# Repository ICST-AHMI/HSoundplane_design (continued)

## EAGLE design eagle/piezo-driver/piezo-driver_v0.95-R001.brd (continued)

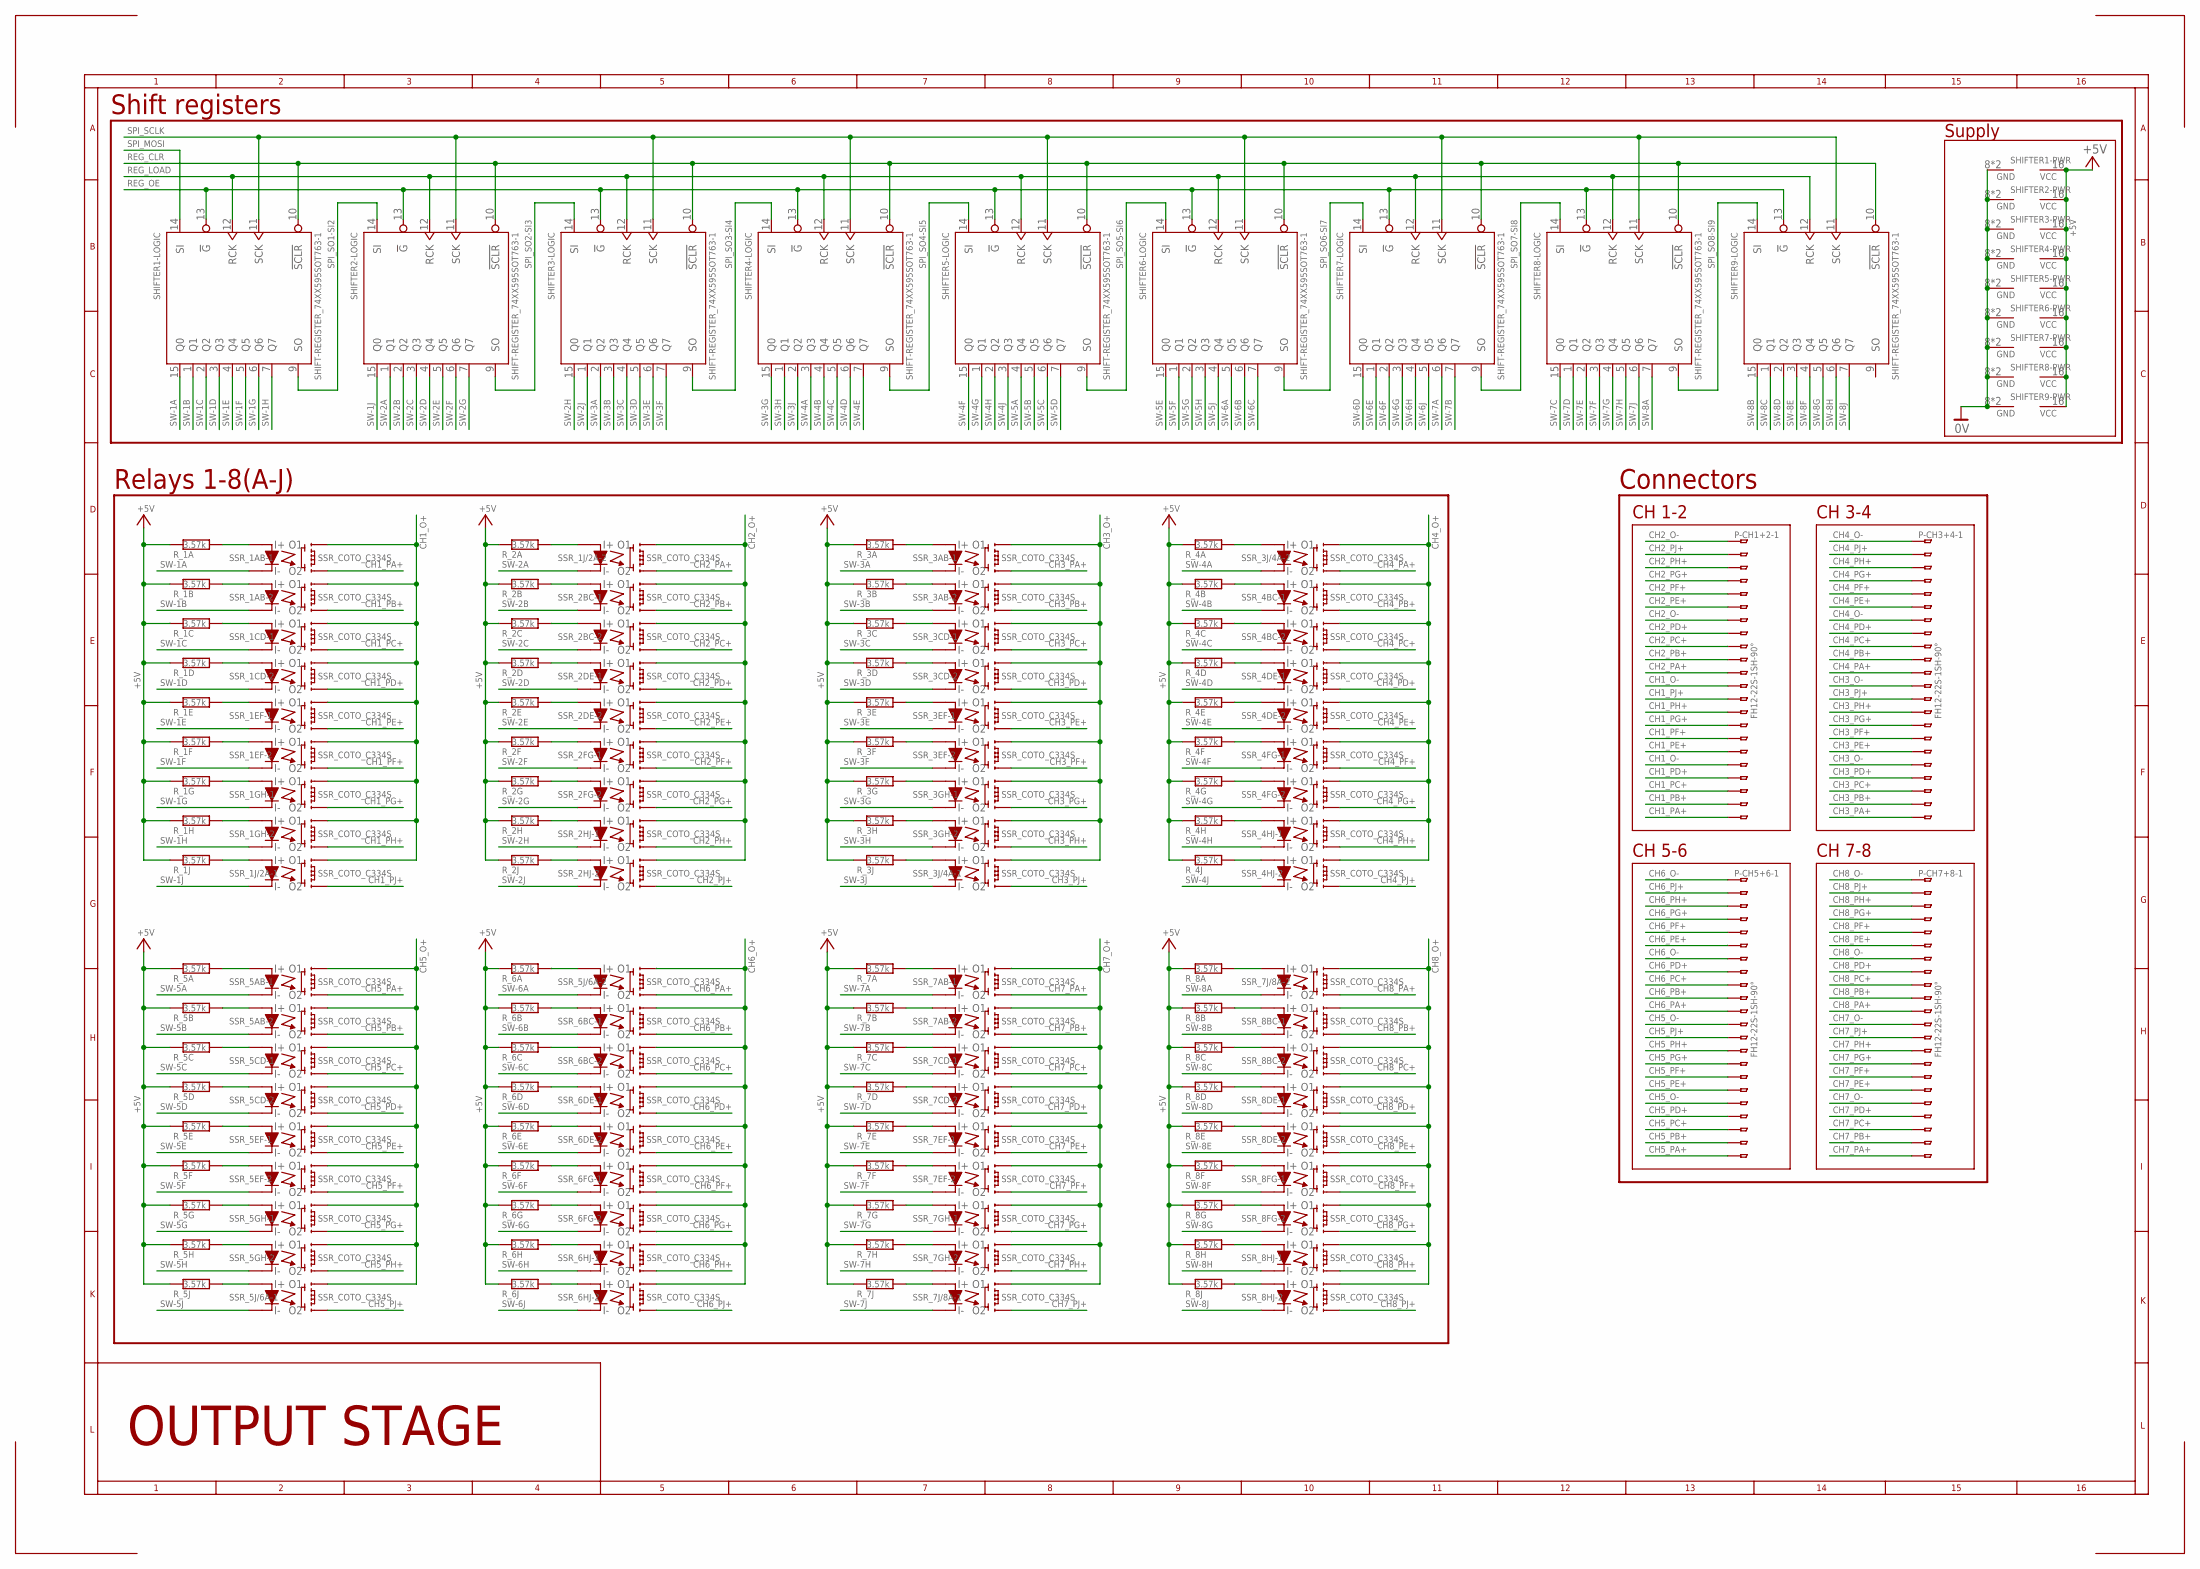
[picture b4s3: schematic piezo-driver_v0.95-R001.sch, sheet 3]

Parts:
P-CH1+2, P-CH3+4, P-CH5+6, P-CH7+8: FH12-22S-1SH-90°; FH12-22S-1SH
R_1A, R_1B, R_1C, R_1D, R_1E, R_1F, R_1G, R_1H, R_1J, R_2A, R_2B, R_2C, R_2D, R_2E, R_2F, R_2G, R_2H, R_2J, R_3A, R_3B, R_3C, R_3D, R_3E, R_3F, R_3G, R_3H, R_3J, R_4A, R_4B, R_4C, R_4D, R_4E, R_4F, R_4G, R_4H, R_4J, R_5A, R_5B, R_5C, R_5D, R_5E, R_5F, R_5G, R_5H, R_5J, R_6A, R_6B, R_6C, R_6D, R_6E, R_6F, R_6G, R_6H, R_6J, R_7A, R_7B, R_7C, R_7D, R_7E, R_7F, R_7G, R_7H, R_7J, R_8A, R_8B, R_8C, R_8D, R_8E, R_8F, R_8G, R_8H, R_8J: 3.57k; R0402
SHIFTER1, SHIFTER2, SHIFTER3, SHIFTER4, SHIFTER5, SHIFTER6, SHIFTER7, SHIFTER8, SHIFTER9: SHIFT-REGISTER_74XX595SOT763-1; SOT763-1
SSR_1AB, SSR_1CD, SSR_1EF, SSR_1GH, SSR_1J/2A, SSR_2BC, SSR_2DE, SSR_2FG, SSR_2HJ, SSR_3AB, SSR_3CD, SSR_3EF, SSR_3GH, SSR_3J/4A, SSR_4BC, SSR_4DE, SSR_4FG, SSR_4HJ, SSR_5AB, SSR_5CD, SSR_5EF, SSR_5GH, SSR_5J/6A, SSR_6BC, SSR_6DE, SSR_6FG, SSR_6HJ, SSR_7AB, SSR_7CD, SSR_7EF, SSR_7GH, SSR_7J/8A, SSR_8BC, SSR_8DE, SSR_8FG, SSR_8HJ: SSR_COTO_C334S; SOP8

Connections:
0V: SHIFTER1.8 (GND), SHIFTER1.PAD (GND), SHIFTER2.8 (GND), SHIFTER2.PAD (GND), SHIFTER3.8 (GND), SHIFTER3.PAD (GND), SHIFTER4.8 (GND), SHIFTER4.PAD (GND), SHIFTER5.8 (GND), SHIFTER5.PAD (GND), SHIFTER6.8 (GND), SHIFTER6.PAD (GND), SHIFTER7.8 (GND), SHIFTER7.PAD (GND), SHIFTER8.8 (GND), SHIFTER8.PAD (GND), SHIFTER9.8 (GND), SHIFTER9.PAD (GND); also elsewhere on the board
+5V: R_1A.2, R_1B.2, R_1C.2, R_1D.2, R_1E.2, R_1F.2, R_1G.2, R_1H.2, R_1J.2, R_2A.2, R_2B.2, R_2C.2, R_2D.2, R_2E.2, R_2F.2, R_2G.2, R_2H.2, R_2J.2, R_3A.2, R_3B.2, R_3C.2, R_3D.2, R_3E.2, R_3F.2, R_3G.2, R_3H.2, R_3J.2, R_4A.2, R_4B.2, R_4C.2, R_4D.2, R_4E.2, R_4F.2, R_4G.2, R_4H.2, R_4J.2, R_5A.2, R_5B.2, R_5C.2, R_5D.2, R_5E.2, R_5F.2, R_5G.2, R_5H.2, R_5J.2, R_6A.2, R_6B.2, R_6C.2, R_6D.2, R_6E.2, R_6F.2, R_6G.2, R_6H.2, R_6J.2, R_7A.2, R_7B.2, R_7C.2, R_7D.2, R_7E.2, R_7F.2, R_7G.2, R_7H.2, R_7J.2, R_8A.2, R_8B.2, R_8C.2, R_8D.2, R_8E.2, R_8F.2, R_8G.2, R_8H.2, R_8J.2, SHIFTER1.16 (VCC), SHIFTER2.16 (VCC), SHIFTER3.16 (VCC), SHIFTER4.16 (VCC), SHIFTER5.16 (VCC), SHIFTER6.16 (VCC), SHIFTER7.16 (VCC), SHIFTER8.16 (VCC), SHIFTER9.16 (VCC); also elsewhere on the board
CH1_O+: SSR_1AB.5 (O1), SSR_1AB.7 (O1), SSR_1CD.5 (O1), SSR_1CD.7 (O1), SSR_1EF.5 (O1), SSR_1EF.7 (O1), SSR_1GH.5 (O1), SSR_1GH.7 (O1), SSR_1J/2A.7 (O1); also elsewhere on the board
CH1_O-: P-CH1+2.12, P-CH1+2.18; also elsewhere on the board
CH1_PA+: P-CH1+2.22, SSR_1AB.8 (O2)
CH1_PB+: P-CH1+2.21, SSR_1AB.6 (O2)
CH1_PC+: P-CH1+2.20, SSR_1CD.8 (O2)
CH1_PD+: P-CH1+2.19, SSR_1CD.6 (O2)
CH1_PE+: P-CH1+2.17, SSR_1EF.8 (O2)
CH1_PF+: P-CH1+2.16, SSR_1EF.6 (O2)
CH1_PG+: P-CH1+2.15, SSR_1GH.8 (O2)
CH1_PH+: P-CH1+2.14, SSR_1GH.6 (O2)
CH1_PJ+: P-CH1+2.13, SSR_1J/2A.8 (O2)
CH2_O+: SSR_1J/2A.5 (O1), SSR_2BC.5 (O1), SSR_2BC.7 (O1), SSR_2DE.5 (O1), SSR_2DE.7 (O1), SSR_2FG.5 (O1), SSR_2FG.7 (O1), SSR_2HJ.5 (O1), SSR_2HJ.7 (O1); also elsewhere on the board
CH2_O-: P-CH1+2.1, P-CH1+2.7; also elsewhere on the board
CH2_PA+: P-CH1+2.11, SSR_1J/2A.6 (O2)
CH2_PB+: P-CH1+2.10, SSR_2BC.8 (O2)
CH2_PC+: P-CH1+2.9, SSR_2BC.6 (O2)
CH2_PD+: P-CH1+2.8, SSR_2DE.8 (O2)
CH2_PE+: P-CH1+2.6, SSR_2DE.6 (O2)
CH2_PF+: P-CH1+2.5, SSR_2FG.8 (O2)
CH2_PG+: P-CH1+2.4, SSR_2FG.6 (O2)
CH2_PH+: P-CH1+2.3, SSR_2HJ.8 (O2)
CH2_PJ+: P-CH1+2.2, SSR_2HJ.6 (O2)
CH3_O+: SSR_3AB.5 (O1), SSR_3AB.7 (O1), SSR_3CD.5 (O1), SSR_3CD.7 (O1), SSR_3EF.5 (O1), SSR_3EF.7 (O1), SSR_3GH.5 (O1), SSR_3GH.7 (O1), SSR_3J/4A.7 (O1); also elsewhere on the board
CH3_O-: P-CH3+4.12, P-CH3+4.18; also elsewhere on the board
CH3_PA+: P-CH3+4.22, SSR_3AB.8 (O2)
CH3_PB+: P-CH3+4.21, SSR_3AB.6 (O2)
CH3_PC+: P-CH3+4.20, SSR_3CD.8 (O2)
CH3_PD+: P-CH3+4.19, SSR_3CD.6 (O2)
CH3_PE+: P-CH3+4.17, SSR_3EF.8 (O2)
CH3_PF+: P-CH3+4.16, SSR_3EF.6 (O2)
CH3_PG+: P-CH3+4.15, SSR_3GH.8 (O2)
CH3_PH+: P-CH3+4.14, SSR_3GH.6 (O2)
CH3_PJ+: P-CH3+4.13, SSR_3J/4A.8 (O2)
CH4_O+: SSR_3J/4A.5 (O1), SSR_4BC.5 (O1), SSR_4BC.7 (O1), SSR_4DE.5 (O1), SSR_4DE.7 (O1), SSR_4FG.5 (O1), SSR_4FG.7 (O1), SSR_4HJ.5 (O1), SSR_4HJ.7 (O1); also elsewhere on the board
CH4_O-: P-CH3+4.1, P-CH3+4.7; also elsewhere on the board
CH4_PA+: P-CH3+4.11, SSR_3J/4A.6 (O2)
CH4_PB+: P-CH3+4.10, SSR_4BC.8 (O2)
CH4_PC+: P-CH3+4.9, SSR_4BC.6 (O2)
CH4_PD+: P-CH3+4.8, SSR_4DE.8 (O2)
CH4_PE+: P-CH3+4.6, SSR_4DE.6 (O2)
CH4_PF+: P-CH3+4.5, SSR_4FG.8 (O2)
CH4_PG+: P-CH3+4.4, SSR_4FG.6 (O2)
CH4_PH+: P-CH3+4.3, SSR_4HJ.8 (O2)
CH4_PJ+: P-CH3+4.2, SSR_4HJ.6 (O2)
CH5_O+: SSR_5AB.5 (O1), SSR_5AB.7 (O1), SSR_5CD.5 (O1), SSR_5CD.7 (O1), SSR_5EF.5 (O1), SSR_5EF.7 (O1), SSR_5GH.5 (O1), SSR_5GH.7 (O1), SSR_5J/6A.7 (O1); also elsewhere on the board
CH5_O-: P-CH5+6.12, P-CH5+6.18; also elsewhere on the board
CH5_PA+: P-CH5+6.22, SSR_5AB.8 (O2)
CH5_PB+: P-CH5+6.21, SSR_5AB.6 (O2)
CH5_PC+: P-CH5+6.20, SSR_5CD.8 (O2)
CH5_PD+: P-CH5+6.19, SSR_5CD.6 (O2)
CH5_PE+: P-CH5+6.17, SSR_5EF.8 (O2)
CH5_PF+: P-CH5+6.16, SSR_5EF.6 (O2)
CH5_PG+: P-CH5+6.15, SSR_5GH.8 (O2)
CH5_PH+: P-CH5+6.14, SSR_5GH.6 (O2)
CH5_PJ+: P-CH5+6.13, SSR_5J/6A.8 (O2)
CH6_O+: SSR_5J/6A.5 (O1), SSR_6BC.5 (O1), SSR_6BC.7 (O1), SSR_6DE.5 (O1), SSR_6DE.7 (O1), SSR_6FG.5 (O1), SSR_6FG.7 (O1), SSR_6HJ.5 (O1), SSR_6HJ.7 (O1); also elsewhere on the board
CH6_O-: P-CH5+6.1, P-CH5+6.7; also elsewhere on the board
CH6_PA+: P-CH5+6.11, SSR_5J/6A.6 (O2)
CH6_PB+: P-CH5+6.10, SSR_6BC.8 (O2)
CH6_PC+: P-CH5+6.9, SSR_6BC.6 (O2)
CH6_PD+: P-CH5+6.8, SSR_6DE.8 (O2)
CH6_PE+: P-CH5+6.6, SSR_6DE.6 (O2)
CH6_PF+: P-CH5+6.5, SSR_6FG.8 (O2)
CH6_PG+: P-CH5+6.4, SSR_6FG.6 (O2)
CH6_PH+: P-CH5+6.3, SSR_6HJ.8 (O2)
CH6_PJ+: P-CH5+6.2, SSR_6HJ.6 (O2)
CH7_O+: SSR_7AB.5 (O1), SSR_7AB.7 (O1), SSR_7CD.5 (O1), SSR_7CD.7 (O1), SSR_7EF.5 (O1), SSR_7EF.7 (O1), SSR_7GH.5 (O1), SSR_7GH.7 (O1), SSR_7J/8A.7 (O1); also elsewhere on the board
CH7_O-: P-CH7+8.12, P-CH7+8.18; also elsewhere on the board
CH7_PA+: P-CH7+8.22, SSR_7AB.8 (O2)
CH7_PB+: P-CH7+8.21, SSR_7AB.6 (O2)
CH7_PC+: P-CH7+8.20, SSR_7CD.8 (O2)
CH7_PD+: P-CH7+8.19, SSR_7CD.6 (O2)
CH7_PE+: P-CH7+8.17, SSR_7EF.8 (O2)
CH7_PF+: P-CH7+8.16, SSR_7EF.6 (O2)
CH7_PG+: P-CH7+8.15, SSR_7GH.8 (O2)
CH7_PH+: P-CH7+8.14, SSR_7GH.6 (O2)
CH7_PJ+: P-CH7+8.13, SSR_7J/8A.8 (O2)
CH8_O+: SSR_7J/8A.5 (O1), SSR_8BC.5 (O1), SSR_8BC.7 (O1), SSR_8DE.5 (O1), SSR_8DE.7 (O1), SSR_8FG.5 (O1), SSR_8FG.7 (O1), SSR_8HJ.5 (O1), SSR_8HJ.7 (O1); also elsewhere on the board
CH8_O-: P-CH7+8.1, P-CH7+8.7; also elsewhere on the board
CH8_PA+: P-CH7+8.11, SSR_7J/8A.6 (O2)
CH8_PB+: P-CH7+8.10, SSR_8BC.8 (O2)
CH8_PC+: P-CH7+8.9, SSR_8BC.6 (O2)
CH8_PD+: P-CH7+8.8, SSR_8DE.8 (O2)
CH8_PE+: P-CH7+8.6, SSR_8DE.6 (O2)
CH8_PF+: P-CH7+8.5, SSR_8FG.8 (O2)
CH8_PG+: P-CH7+8.4, SSR_8FG.6 (O2)
CH8_PH+: P-CH7+8.3, SSR_8HJ.8 (O2)
CH8_PJ+: P-CH7+8.2, SSR_8HJ.6 (O2)
unnamed: R_3A.1, SSR_3AB.1 (I+)
unnamed: R_3B.1, SSR_3AB.3 (I+)
unnamed: R_3C.1, SSR_3CD.1 (I+)
unnamed: R_3D.1, SSR_3CD.3 (I+)
unnamed: R_3E.1, SSR_3EF.1 (I+)
unnamed: R_3F.1, SSR_3EF.3 (I+)
unnamed: R_3G.1, SSR_3GH.1 (I+)
unnamed: R_3H.1, SSR_3GH.3 (I+)
unnamed: R_3J.1, SSR_3J/4A.1 (I+)
unnamed: R_4A.1, SSR_3J/4A.3 (I+)
unnamed: R_4B.1, SSR_4BC.1 (I+)
unnamed: R_4C.1, SSR_4BC.3 (I+)
unnamed: R_4D.1, SSR_4DE.1 (I+)
unnamed: R_4E.1, SSR_4DE.3 (I+)
unnamed: R_4F.1, SSR_4FG.1 (I+)
unnamed: R_4J.1, SSR_4HJ.3 (I+)
unnamed: R_4H.1, SSR_4HJ.1 (I+)
unnamed: R_4G.1, SSR_4FG.3 (I+)
unnamed: R_5A.1, SSR_5AB.1 (I+)
unnamed: R_5B.1, SSR_5AB.3 (I+)
unnamed: R_5C.1, SSR_5CD.1 (I+)
unnamed: R_5D.1, SSR_5CD.3 (I+)
unnamed: R_5E.1, SSR_5EF.1 (I+)
unnamed: R_5F.1, SSR_5EF.3 (I+)
unnamed: R_5G.1, SSR_5GH.1 (I+)
unnamed: R_5H.1, SSR_5GH.3 (I+)
unnamed: R_5J.1, SSR_5J/6A.1 (I+)
unnamed: R_6A.1, SSR_5J/6A.3 (I+)
unnamed: R_6B.1, SSR_6BC.1 (I+)
unnamed: R_6C.1, SSR_6BC.3 (I+)
unnamed: R_6D.1, SSR_6DE.1 (I+)
unnamed: R_6E.1, SSR_6DE.3 (I+)
unnamed: R_6F.1, SSR_6FG.1 (I+)
unnamed: R_6J.1, SSR_6HJ.3 (I+)
unnamed: R_6H.1, SSR_6HJ.1 (I+)
unnamed: R_6G.1, SSR_6FG.3 (I+)
unnamed: R_7A.1, SSR_7AB.1 (I+)
unnamed: R_7B.1, SSR_7AB.3 (I+)
unnamed: R_7C.1, SSR_7CD.1 (I+)
unnamed: R_7D.1, SSR_7CD.3 (I+)
unnamed: R_7E.1, SSR_7EF.1 (I+)
unnamed: R_1A.1, SSR_1AB.1 (I+)
unnamed: R_1B.1, SSR_1AB.3 (I+)
unnamed: R_7F.1, SSR_7EF.3 (I+)
unnamed: R_7G.1, SSR_7GH.1 (I+)
unnamed: R_1C.1, SSR_1CD.1 (I+)
unnamed: R_1D.1, SSR_1CD.3 (I+)
unnamed: R_1E.1, SSR_1EF.1 (I+)
unnamed: R_1F.1, SSR_1EF.3 (I+)
unnamed: R_1G.1, SSR_1GH.1 (I+)
unnamed: R_1H.1, SSR_1GH.3 (I+)
unnamed: R_1J.1, SSR_1J/2A.1 (I+)
unnamed: R_2A.1, SSR_1J/2A.3 (I+)
unnamed: R_2B.1, SSR_2BC.1 (I+)
unnamed: R_2C.1, SSR_2BC.3 (I+)
unnamed: R_7H.1, SSR_7GH.3 (I+)
unnamed: R_7J.1, SSR_7J/8A.1 (I+)
unnamed: R_8A.1, SSR_7J/8A.3 (I+)
unnamed: R_8B.1, SSR_8BC.1 (I+)
unnamed: R_8C.1, SSR_8BC.3 (I+)
unnamed: R_8D.1, SSR_8DE.1 (I+)
unnamed: R_8E.1, SSR_8DE.3 (I+)
unnamed: R_8F.1, SSR_8FG.1 (I+)
unnamed: R_8J.1, SSR_8HJ.3 (I+)
unnamed: R_2D.1, SSR_2DE.1 (I+)
unnamed: R_2E.1, SSR_2DE.3 (I+)
unnamed: R_2F.1, SSR_2FG.1 (I+)
unnamed: R_2J.1, SSR_2HJ.3 (I+)
unnamed: R_2H.1, SSR_2HJ.1 (I+)
unnamed: R_2G.1, SSR_2FG.3 (I+)
unnamed: R_8H.1, SSR_8HJ.1 (I+)
unnamed: R_8G.1, SSR_8FG.3 (I+)
REG_CLR: SHIFTER1.10 (!SCLR), SHIFTER2.10 (!SCLR), SHIFTER3.10 (!SCLR), SHIFTER4.10 (!SCLR), SHIFTER5.10 (!SCLR), SHIFTER6.10 (!SCLR), SHIFTER7.10 (!SCLR), SHIFTER8.10 (!SCLR), SHIFTER9.10 (!SCLR); also elsewhere on the board
REG_LOAD: SHIFTER1.12 (RCK), SHIFTER2.12 (RCK), SHIFTER3.12 (RCK), SHIFTER4.12 (RCK), SHIFTER5.12 (RCK), SHIFTER6.12 (RCK), SHIFTER7.12 (RCK), SHIFTER8.12 (RCK), SHIFTER9.12 (RCK); also elsewhere on the board
REG_OE: SHIFTER1.13 (!G), SHIFTER2.13 (!G), SHIFTER3.13 (!G), SHIFTER4.13 (!G), SHIFTER5.13 (!G), SHIFTER6.13 (!G), SHIFTER7.13 (!G), SHIFTER8.13 (!G), SHIFTER9.13 (!G); also elsewhere on the board
SPI_MOSI: SHIFTER1.14 (SI); also elsewhere on the board
SPI_SCLK: SHIFTER1.11 (SCK), SHIFTER2.11 (SCK), SHIFTER3.11 (SCK), SHIFTER4.11 (SCK), SHIFTER5.11 (SCK), SHIFTER6.11 (SCK), SHIFTER7.11 (SCK), SHIFTER8.11 (SCK), SHIFTER9.11 (SCK); also elsewhere on the board
SPI_SO1-SI2: SHIFTER1.9 (SO), SHIFTER2.14 (SI)
SPI_SO2-SI3: SHIFTER2.9 (SO), SHIFTER3.14 (SI)
SPI_SO3-SI4: SHIFTER3.9 (SO), SHIFTER4.14 (SI)
SPI_SO4-SI5: SHIFTER4.9 (SO), SHIFTER5.14 (SI)
SPI_SO5-SI6: SHIFTER5.9 (SO), SHIFTER6.14 (SI)
SPI_SO6-SI7: SHIFTER6.9 (SO), SHIFTER7.14 (SI)
SPI_SO7-SI8: SHIFTER7.9 (SO), SHIFTER8.14 (SI)
SPI_SO8-SI9: SHIFTER8.9 (SO), SHIFTER9.14 (SI)
SW-1A: SHIFTER1.15 (Q0), SSR_1AB.2 (I-)
SW-1B: SHIFTER1.1 (Q1), SSR_1AB.4 (I-)
SW-1C: SHIFTER1.2 (Q2), SSR_1CD.2 (I-)
SW-1D: SHIFTER1.3 (Q3), SSR_1CD.4 (I-)
SW-1E: SHIFTER1.4 (Q4), SSR_1EF.2 (I-)
SW-1F: SHIFTER1.5 (Q5), SSR_1EF.4 (I-)
SW-1G: SHIFTER1.6 (Q6), SSR_1GH.2 (I-)
SW-1H: SHIFTER1.7 (Q7), SSR_1GH.4 (I-)
SW-1J: SHIFTER2.15 (Q0), SSR_1J/2A.2 (I-)
SW-2A: SHIFTER2.1 (Q1), SSR_1J/2A.4 (I-)
SW-2B: SHIFTER2.2 (Q2), SSR_2BC.2 (I-)
SW-2C: SHIFTER2.3 (Q3), SSR_2BC.4 (I-)
SW-2D: SHIFTER2.4 (Q4), SSR_2DE.2 (I-)
SW-2E: SHIFTER2.5 (Q5), SSR_2DE.4 (I-)
SW-2F: SHIFTER2.6 (Q6), SSR_2FG.2 (I-)
SW-2G: SHIFTER2.7 (Q7), SSR_2FG.4 (I-)
SW-2H: SHIFTER3.15 (Q0), SSR_2HJ.2 (I-)
SW-2J: SHIFTER3.1 (Q1), SSR_2HJ.4 (I-)
SW-3A: SHIFTER3.2 (Q2), SSR_3AB.2 (I-)
SW-3B: SHIFTER3.3 (Q3), SSR_3AB.4 (I-)
SW-3C: SHIFTER3.4 (Q4), SSR_3CD.2 (I-)
SW-3D: SHIFTER3.5 (Q5), SSR_3CD.4 (I-)
SW-3E: SHIFTER3.6 (Q6), SSR_3EF.2 (I-)
SW-3F: SHIFTER3.7 (Q7), SSR_3EF.4 (I-)
SW-3G: SHIFTER4.15 (Q0), SSR_3GH.2 (I-)
SW-3H: SHIFTER4.1 (Q1), SSR_3GH.4 (I-)
SW-3J: SHIFTER4.2 (Q2), SSR_3J/4A.2 (I-)
SW-4A: SHIFTER4.3 (Q3), SSR_3J/4A.4 (I-)
SW-4B: SHIFTER4.4 (Q4), SSR_4BC.2 (I-)
SW-4C: SHIFTER4.5 (Q5), SSR_4BC.4 (I-)
SW-4D: SHIFTER4.6 (Q6), SSR_4DE.2 (I-)
SW-4E: SHIFTER4.7 (Q7), SSR_4DE.4 (I-)
SW-4F: SHIFTER5.15 (Q0), SSR_4FG.2 (I-)
SW-4G: SHIFTER5.1 (Q1), SSR_4FG.4 (I-)
SW-4H: SHIFTER5.2 (Q2), SSR_4HJ.2 (I-)
SW-4J: SHIFTER5.3 (Q3), SSR_4HJ.4 (I-)
SW-5A: SHIFTER5.4 (Q4), SSR_5AB.2 (I-)
SW-5B: SHIFTER5.5 (Q5), SSR_5AB.4 (I-)
SW-5C: SHIFTER5.6 (Q6), SSR_5CD.2 (I-)
SW-5D: SHIFTER5.7 (Q7), SSR_5CD.4 (I-)
SW-5E: SHIFTER6.15 (Q0), SSR_5EF.2 (I-)
SW-5F: SHIFTER6.1 (Q1), SSR_5EF.4 (I-)
SW-5G: SHIFTER6.2 (Q2), SSR_5GH.2 (I-)
SW-5H: SHIFTER6.3 (Q3), SSR_5GH.4 (I-)
SW-5J: SHIFTER6.4 (Q4), SSR_5J/6A.2 (I-)
SW-6A: SHIFTER6.5 (Q5), SSR_5J/6A.4 (I-)
SW-6B: SHIFTER6.6 (Q6), SSR_6BC.2 (I-)
SW-6C: SHIFTER6.7 (Q7), SSR_6BC.4 (I-)
SW-6D: SHIFTER7.15 (Q0), SSR_6DE.2 (I-)
SW-6E: SHIFTER7.1 (Q1), SSR_6DE.4 (I-)
SW-6F: SHIFTER7.2 (Q2), SSR_6FG.2 (I-)
SW-6G: SHIFTER7.3 (Q3), SSR_6FG.4 (I-)
SW-6H: SHIFTER7.4 (Q4), SSR_6HJ.2 (I-)
SW-6J: SHIFTER7.5 (Q5), SSR_6HJ.4 (I-)
SW-7A: SHIFTER7.6 (Q6), SSR_7AB.2 (I-)
SW-7B: SHIFTER7.7 (Q7), SSR_7AB.4 (I-)
SW-7C: SHIFTER8.15 (Q0), SSR_7CD.2 (I-)
SW-7D: SHIFTER8.1 (Q1), SSR_7CD.4 (I-)
SW-7E: SHIFTER8.2 (Q2), SSR_7EF.2 (I-)
SW-7F: SHIFTER8.3 (Q3), SSR_7EF.4 (I-)
SW-7G: SHIFTER8.4 (Q4), SSR_7GH.2 (I-)
SW-7H: SHIFTER8.5 (Q5), SSR_7GH.4 (I-)
SW-7J: SHIFTER8.6 (Q6), SSR_7J/8A.2 (I-)
SW-8A: SHIFTER8.7 (Q7), SSR_7J/8A.4 (I-)
SW-8B: SHIFTER9.15 (Q0), SSR_8BC.2 (I-)
SW-8C: SHIFTER9.1 (Q1), SSR_8BC.4 (I-)
SW-8D: SHIFTER9.2 (Q2), SSR_8DE.2 (I-)
SW-8E: SHIFTER9.3 (Q3), SSR_8DE.4 (I-)
SW-8F: SHIFTER9.4 (Q4), SSR_8FG.2 (I-)
SW-8G: SHIFTER9.5 (Q5), SSR_8FG.4 (I-)
SW-8H: SHIFTER9.6 (Q6), SSR_8HJ.2 (I-)
SW-8J: SHIFTER9.7 (Q7), SSR_8HJ.4 (I-)

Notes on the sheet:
OUTPUT STAGE
Relays 1-8(A-J)
Shift registers
Supply
Connectors
CH 1-2
CH 3-4
CH 5-6
CH 7-8

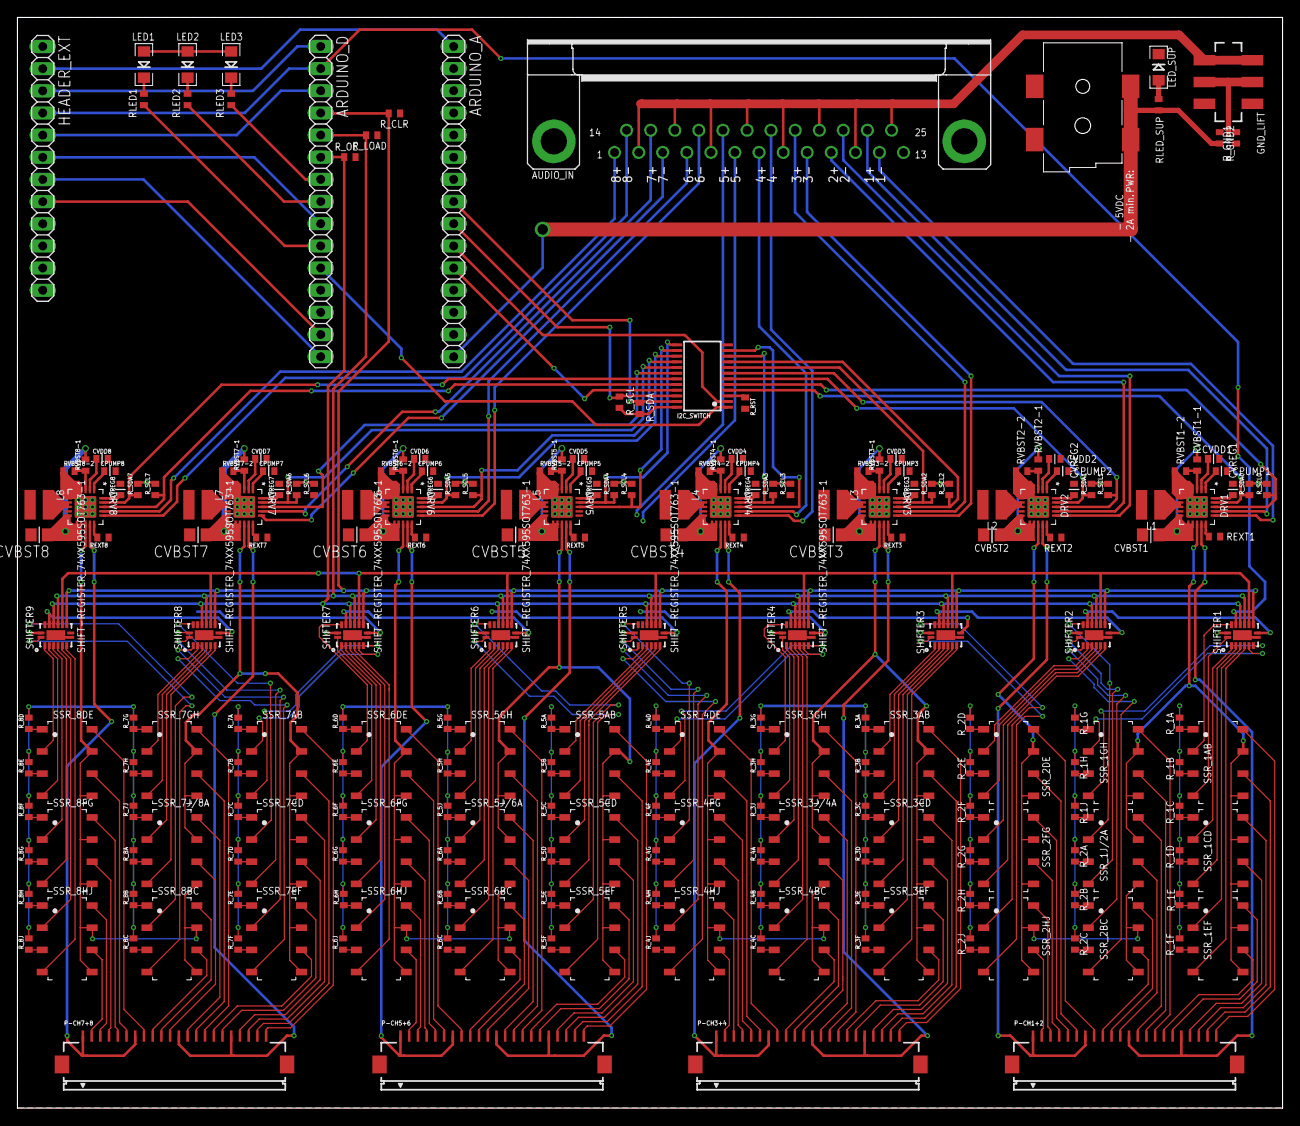
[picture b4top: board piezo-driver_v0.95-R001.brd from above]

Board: 2 copper layers, 145.0 x 125.0 mm, 232 parts (0 on the bottom side), 347 nets.

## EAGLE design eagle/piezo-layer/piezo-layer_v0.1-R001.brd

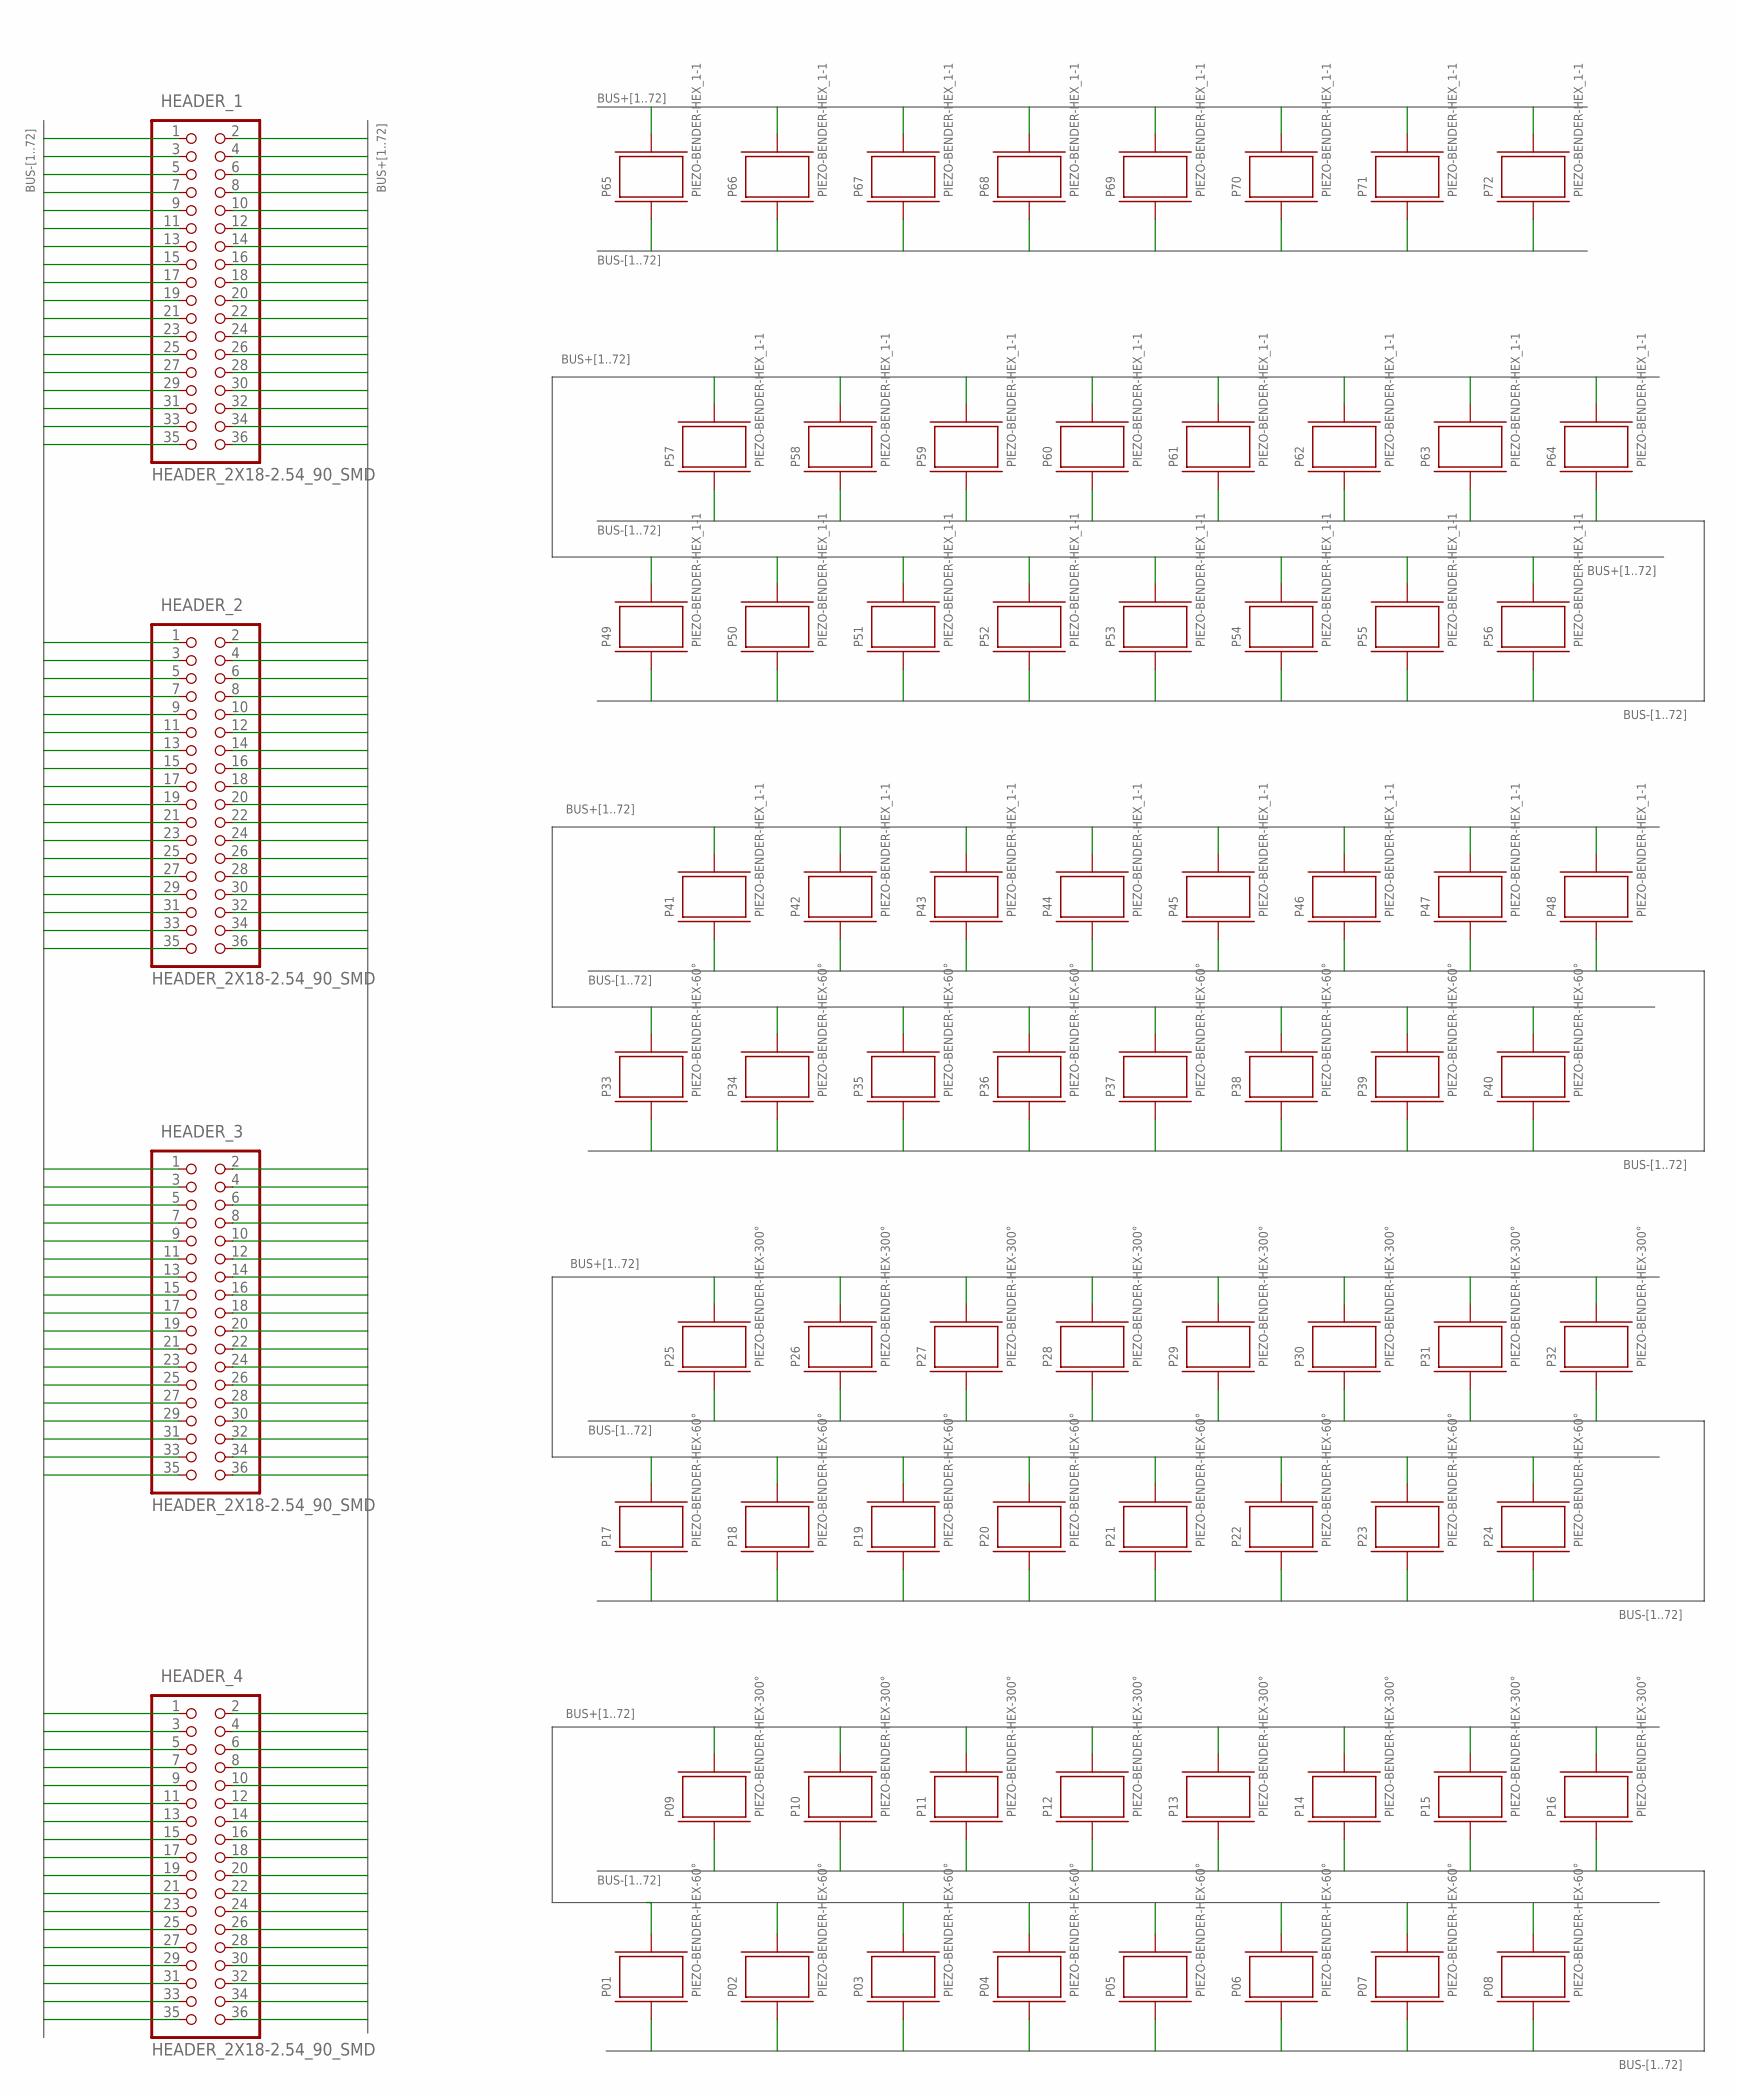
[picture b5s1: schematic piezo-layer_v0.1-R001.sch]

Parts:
HEADER_1, HEADER_2, HEADER_3, HEADER_4: HEADER_2X18-2.54_90_SMD; 2X18_2.54_90_SMD
P01, P02, P03, P04, P05, P06, P07, P08, P17, P18, P19, P20, P21, P22, P23, P24, P33, P34, P35, P36, P37, P38, P39, P40: PIEZO-BENDER-HEX-60°; PIEZO-BENDER-HEX_16MM_60°
P09, P10, P11, P12, P13, P14, P15, P16, P25, P26, P27, P28, P29, P30, P31, P32: PIEZO-BENDER-HEX-300°; PIEZO-BENDER-HEX_16MM_300°
P41, P42, P43, P44, P45, P46, P47, P48, P49, P50, P51, P52, P53, P54, P55, P56, P57, P58, P59, P60, P61, P62, P63, P64, P65, P66, P67, P68, P69, P70, P71, P72: PIEZO-BENDER-HEX_1-1; PIEZO-BENDER-HEX_16MM_1+_1-

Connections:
BUS+1: HEADER_1.18, P01.TIP1 (+_1)
BUS+2: HEADER_1.36, P02.TIP1 (+_1)
BUS+3: HEADER_2.18, P03.TIP1 (+_1)
BUS+4: HEADER_2.36, P04.TIP1 (+_1)
BUS+5: HEADER_3.18, P05.TIP1 (+_1)
BUS+6: HEADER_3.36, P06.TIP1 (+_1)
BUS+7: HEADER_4.18, P07.TIP1 (+_1)
BUS+8: HEADER_4.36, P08.TIP1 (+_1)
BUS+9: HEADER_1.16, P09.TIP1 (+_1)
BUS+10: HEADER_1.34, P10.TIP1 (+_1)
BUS+11: HEADER_2.16, P11.TIP1 (+_1)
BUS+12: HEADER_2.34, P12.TIP1 (+_1)
BUS+13: HEADER_3.16, P13.TIP1 (+_1)
BUS+14: HEADER_3.34, P14.TIP1 (+_1)
BUS+15: HEADER_4.16, P15.TIP1 (+_1)
BUS+16: HEADER_4.34, P16.TIP1 (+_1)
BUS+17: HEADER_1.14, P17.TIP1 (+_1)
BUS+18: HEADER_1.32, P18.TIP1 (+_1)
BUS+19: HEADER_2.14, P19.TIP1 (+_1)
BUS+20: HEADER_2.32, P20.TIP1 (+_1)
BUS+21: HEADER_3.14, P21.TIP1 (+_1)
BUS+22: HEADER_3.32, P22.TIP1 (+_1)
BUS+23: HEADER_4.14, P23.TIP1 (+_1)
BUS+24: HEADER_4.32, P24.TIP1 (+_1)
BUS+25: HEADER_1.12, P25.TIP1 (+_1)
BUS+26: HEADER_1.30, P26.TIP1 (+_1)
BUS+27: HEADER_2.12, P27.TIP1 (+_1)
BUS+28: HEADER_2.30, P28.TIP1 (+_1)
BUS+29: HEADER_3.12, P29.TIP1 (+_1)
BUS+30: HEADER_3.30, P30.TIP1 (+_1)
BUS+31: HEADER_4.12, P31.TIP1 (+_1)
BUS+32: HEADER_4.30, P32.TIP1 (+_1)
BUS+33: HEADER_1.10, P33.TIP1 (+_1)
BUS+34: HEADER_1.28, P34.TIP1 (+_1)
BUS+35: HEADER_2.10, P35.TIP1 (+_1)
BUS+36: HEADER_2.28, P36.TIP1 (+_1)
BUS+37: HEADER_3.10, P37.TIP1 (+_1)
BUS+38: HEADER_3.28, P38.TIP1 (+_1)
BUS+39: HEADER_4.10, P39.TIP1 (+_1)
BUS+40: HEADER_4.28, P40.TIP1 (+_1)
BUS+41: HEADER_1.8, P41.TIP1 (+_1)
BUS+42: HEADER_1.26, P42.TIP1 (+_1)
BUS+43: HEADER_2.8, P43.TIP1 (+_1)
BUS+44: HEADER_2.26, P44.TIP1 (+_1)
BUS+45: HEADER_3.8, P45.TIP1 (+_1)
BUS+46: HEADER_3.26, P46.TIP1 (+_1)
BUS+47: HEADER_4.8, P47.TIP1 (+_1)
BUS+48: HEADER_4.26, P48.TIP1 (+_1)
BUS+49: HEADER_1.6, P49.TIP1 (+_1)
BUS+50: HEADER_1.24, P50.TIP1 (+_1)
BUS+51: HEADER_2.6, P51.TIP1 (+_1)
BUS+52: HEADER_2.24, P52.TIP1 (+_1)
BUS+53: HEADER_3.6, P53.TIP1 (+_1)
BUS+54: HEADER_3.24, P54.TIP1 (+_1)
BUS+55: HEADER_4.6, P55.TIP1 (+_1)
BUS+56: HEADER_4.24, P56.TIP1 (+_1)
BUS+57: HEADER_1.4, P57.TIP1 (+_1)
BUS+58: HEADER_1.22, P58.TIP1 (+_1)
BUS+59: HEADER_2.4, P59.TIP1 (+_1)
BUS+60: HEADER_2.22, P60.TIP1 (+_1)
BUS+61: HEADER_3.4, P61.TIP1 (+_1)
BUS+62: HEADER_3.22, P62.TIP1 (+_1)
BUS+63: HEADER_4.4, P63.TIP1 (+_1)
BUS+64: HEADER_4.22, P64.TIP1 (+_1)
BUS+65: HEADER_1.2, P65.TIP1 (+_1)
BUS+66: HEADER_1.20, P66.TIP1 (+_1)
BUS+67: HEADER_2.2, P67.TIP1 (+_1)
BUS+68: HEADER_2.20, P68.TIP1 (+_1)
BUS+69: HEADER_3.2, P69.TIP1 (+_1)
BUS+70: HEADER_3.20, P70.TIP1 (+_1)
BUS+71: HEADER_4.2, P71.TIP1 (+_1)
BUS+72: HEADER_4.20, P72.TIP1 (+_1)
BUS-1: HEADER_1.17, P01.PAD1 (-_1)
BUS-2: HEADER_1.35, P02.PAD1 (-_1)
BUS-3: HEADER_2.17, P03.PAD1 (-_1)
BUS-4: HEADER_2.35, P04.PAD1 (-_1)
BUS-5: HEADER_3.17, P05.PAD1 (-_1)
BUS-6: HEADER_3.35, P06.PAD1 (-_1)
BUS-7: HEADER_4.17, P07.PAD1 (-_1)
BUS-8: HEADER_4.35, P08.PAD1 (-_1)
BUS-9: HEADER_1.15, P09.PAD1 (-_1)
BUS-10: HEADER_1.33, P10.PAD1 (-_1)
BUS-11: HEADER_2.15, P11.PAD1 (-_1)
BUS-12: HEADER_2.33, P12.PAD1 (-_1)
BUS-13: HEADER_3.15, P13.PAD1 (-_1)
BUS-14: HEADER_3.33, P14.PAD1 (-_1)
BUS-15: HEADER_4.15, P15.PAD1 (-_1)
BUS-16: HEADER_4.33, P16.PAD1 (-_1)
BUS-17: HEADER_1.13, P17.PAD1 (-_1)
BUS-18: HEADER_1.31, P18.PAD1 (-_1)
BUS-19: HEADER_2.13, P19.PAD1 (-_1)
BUS-20: HEADER_2.31, P20.PAD1 (-_1)
BUS-21: HEADER_3.13, P21.PAD1 (-_1)
BUS-22: HEADER_3.31, P22.PAD1 (-_1)
BUS-23: HEADER_4.13, P23.PAD1 (-_1)
BUS-24: HEADER_4.31, P24.PAD1 (-_1)
BUS-25: HEADER_1.11, P25.PAD1 (-_1)
BUS-26: HEADER_1.29, P26.PAD1 (-_1)
BUS-27: HEADER_2.11, P27.PAD1 (-_1)
BUS-28: HEADER_2.29, P28.PAD1 (-_1)
BUS-29: HEADER_3.11, P29.PAD1 (-_1)
BUS-30: HEADER_3.29, P30.PAD1 (-_1)
BUS-31: HEADER_4.11, P31.PAD1 (-_1)
BUS-32: HEADER_4.29, P32.PAD1 (-_1)
BUS-33: HEADER_1.9, P33.PAD1 (-_1)
BUS-34: HEADER_1.27, P34.PAD1 (-_1)
BUS-35: HEADER_2.9, P35.PAD1 (-_1)
BUS-36: HEADER_2.27, P36.PAD1 (-_1)
BUS-37: HEADER_3.9, P37.PAD1 (-_1)
BUS-38: HEADER_3.27, P38.PAD1 (-_1)
BUS-39: HEADER_4.9, P39.PAD1 (-_1)
BUS-40: HEADER_4.27, P40.PAD1 (-_1)
BUS-41: HEADER_1.7, P41.PAD1 (-_1)
BUS-42: HEADER_1.25, P42.PAD1 (-_1)
BUS-43: HEADER_2.7, P43.PAD1 (-_1)
BUS-44: HEADER_2.25, P44.PAD1 (-_1)
BUS-45: HEADER_3.7, P45.PAD1 (-_1)
BUS-46: HEADER_3.25, P46.PAD1 (-_1)
BUS-47: HEADER_4.7, P47.PAD1 (-_1)
BUS-48: HEADER_4.25, P48.PAD1 (-_1)
BUS-49: HEADER_1.5, P49.PAD1 (-_1)
BUS-50: HEADER_1.23, P50.PAD1 (-_1)
BUS-51: HEADER_2.5, P51.PAD1 (-_1)
BUS-52: HEADER_2.23, P52.PAD1 (-_1)
BUS-53: HEADER_3.5, P53.PAD1 (-_1)
BUS-54: HEADER_3.23, P54.PAD1 (-_1)
BUS-55: HEADER_4.5, P55.PAD1 (-_1)
BUS-56: HEADER_4.23, P56.PAD1 (-_1)
BUS-57: HEADER_1.3, P57.PAD1 (-_1)
BUS-58: HEADER_1.21, P58.PAD1 (-_1)
BUS-59: HEADER_2.3, P59.PAD1 (-_1)
BUS-60: HEADER_2.21, P60.PAD1 (-_1)
BUS-61: HEADER_3.3, P61.PAD1 (-_1)
BUS-62: HEADER_3.21, P62.PAD1 (-_1)
BUS-63: HEADER_4.3, P63.PAD1 (-_1)
BUS-64: HEADER_4.21, P64.PAD1 (-_1)
BUS-65: HEADER_1.1, P65.PAD1 (-_1)
BUS-66: HEADER_1.19, P66.PAD1 (-_1)
BUS-67: HEADER_2.1, P67.PAD1 (-_1)
BUS-68: HEADER_2.19, P68.PAD1 (-_1)
BUS-69: HEADER_3.1, P69.PAD1 (-_1)
BUS-70: HEADER_3.19, P70.PAD1 (-_1)
BUS-71: HEADER_4.1, P71.PAD1 (-_1)
BUS-72: HEADER_4.19, P72.PAD1 (-_1)

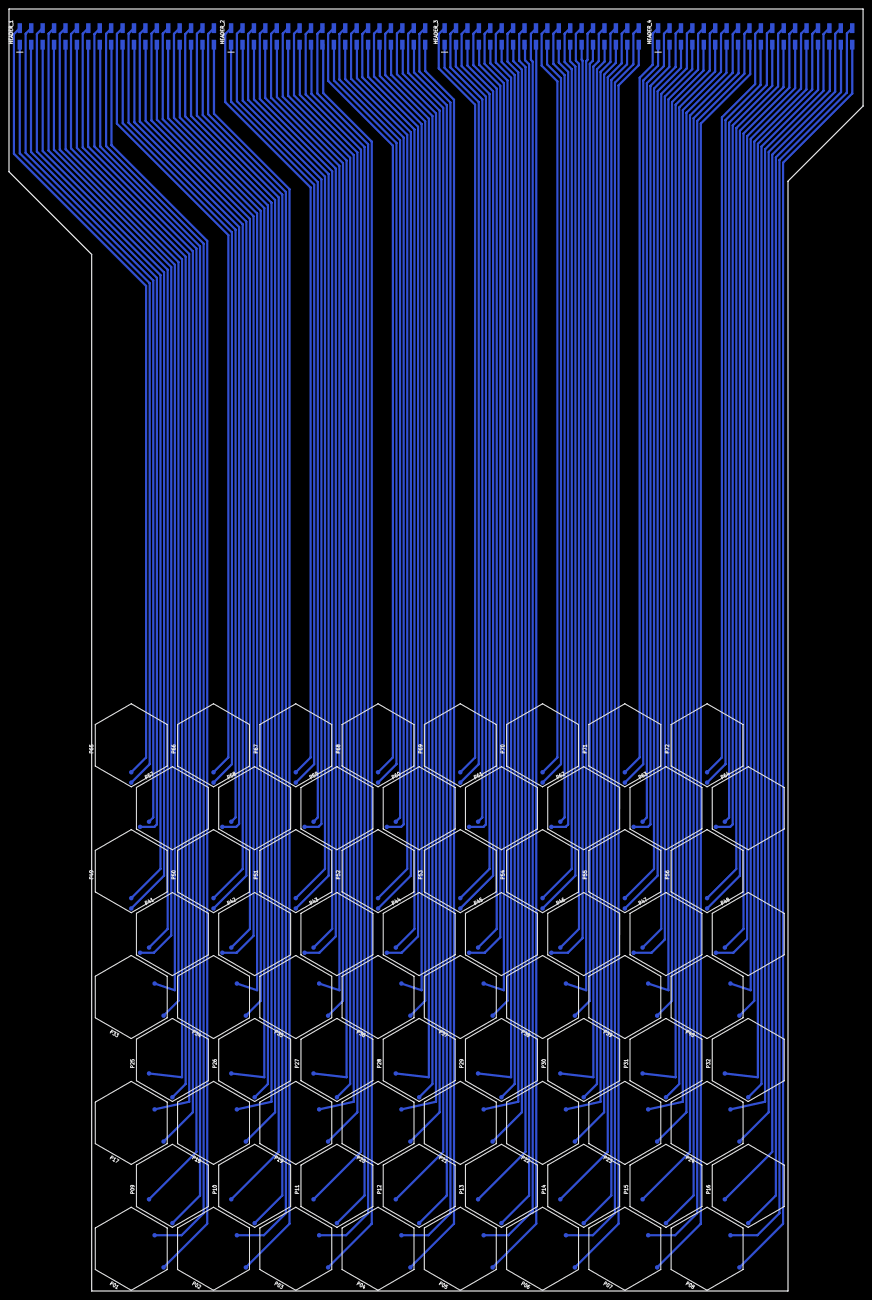
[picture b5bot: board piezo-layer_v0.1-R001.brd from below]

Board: 2 copper layers, 190.0 x 285.2 mm, 76 parts (76 on the bottom side), 144 nets.
